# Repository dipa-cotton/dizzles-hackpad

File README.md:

# dizzles-hackpad
MACROPAD FOR BLUEPRINT YAYAY- I created a macropad using 5 switches, 1 RP2040, and 2 LEDs. I followed the tutorial to a T and simply added an extra switch, but this is version 1 of hopefully more versions to come!

## Challenges
This was my first time using KiCAD, and wiring the PCB was a pain. I had to redo it around seven times because I kept missing one route. This is my very first Hackpad, I'm planning to make more complex ones in the future :)

## BOM:
- 5x Cherry MX Switches
- 2x SK6812 MINI Leds
- 1x XIAO RP2040
- 4x Blank DSA Keycaps
- 4x M3x16 Bolt
- 4x M3 Heatset

ITS SO EXPENSIVE T-T everything comes in bulk but I'm planning to make more macropads in the future so at least they'll be put to use- OR LMK IF YOU CAN FIND ANYTHING CHEAPER

## Others:
- KMK Firmware
- Top Case.stl
- Bottom Case.stl

## Pictures!:

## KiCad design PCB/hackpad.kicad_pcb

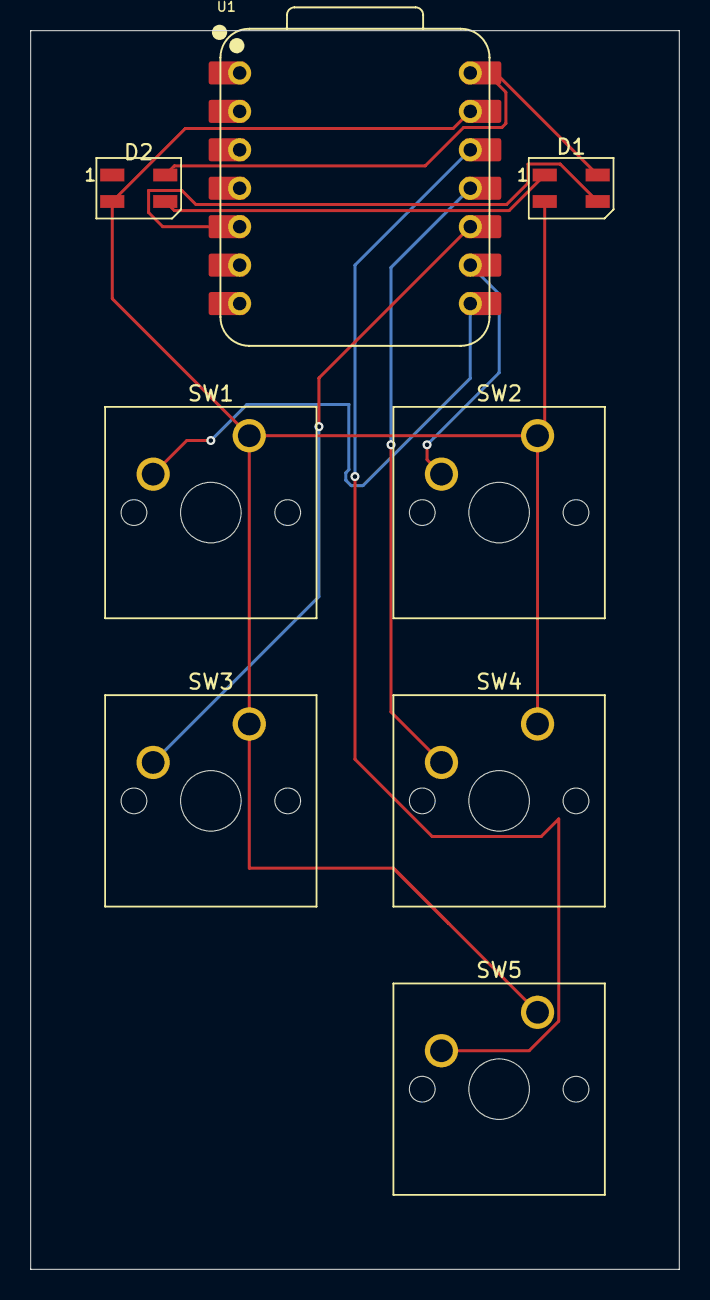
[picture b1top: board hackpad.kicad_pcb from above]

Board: 2 copper layers, 42.9 x 81.9 mm, 8 parts (0 on the bottom side), 9 nets.

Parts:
D1, D2: SK6812MINI; LED_SK6812MINI_PLCC4_3.5x3.5mm_P1.75mm
SW1, SW2, SW3, SW4, SW5: SW_Push; SW_Cherry_MX_1.00u_PCB
U1: XIAO-RP2040-DIP

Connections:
+5V: D1.4 (VDD), D2.4 (VDD), U1.14 (VBUS)
GND: D1.2 (VSS), D2.2 (VSS), SW1.1, SW2.1, SW3.1, SW4.1, SW5.1, U1.13 (GND)
unnamed: D1.3 (DIN), U1.5 (GPIO6/SDA)
unnamed: D1.1 (DOUT), D2.3 (DIN)
unnamed: SW5.2, U1.12 (3V3)
unnamed: SW1.2, U1.8 (GPIO1/RX)
unnamed: SW2.2, U1.9 (GPIO2/SCK)
unnamed: SW4.2, U1.11 (GPIO3/MOSI)
unnamed: SW3.2, U1.10 (GPIO4/MISO)

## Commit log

2025-11-22 Create dsdkfjdslk
2025-11-22 Create ah
2025-11-22 Create see
2025-11-22 Create Part List Explanation
2025-11-22 Add explanations for CAD part files
2025-11-22 Create KiCAD stuff
2025-11-22 Create Firmware
2025-11-22 Update README with project overview and BOM
    Added project details, challenges faced, and BOM for the macropad.
2025-11-22 Update README formatting and section headers
2025-11-22 Update README with project details and sections
2025-11-22 Refactor section headers in README.md
    Updated section headers in README.md for consistency.
2025-11-22 Revise BOM and add Pictures section in README
    Updated the Bill of Materials (BOM) and added a Pictures section.
2025-11-22 Update README with additional images and items
